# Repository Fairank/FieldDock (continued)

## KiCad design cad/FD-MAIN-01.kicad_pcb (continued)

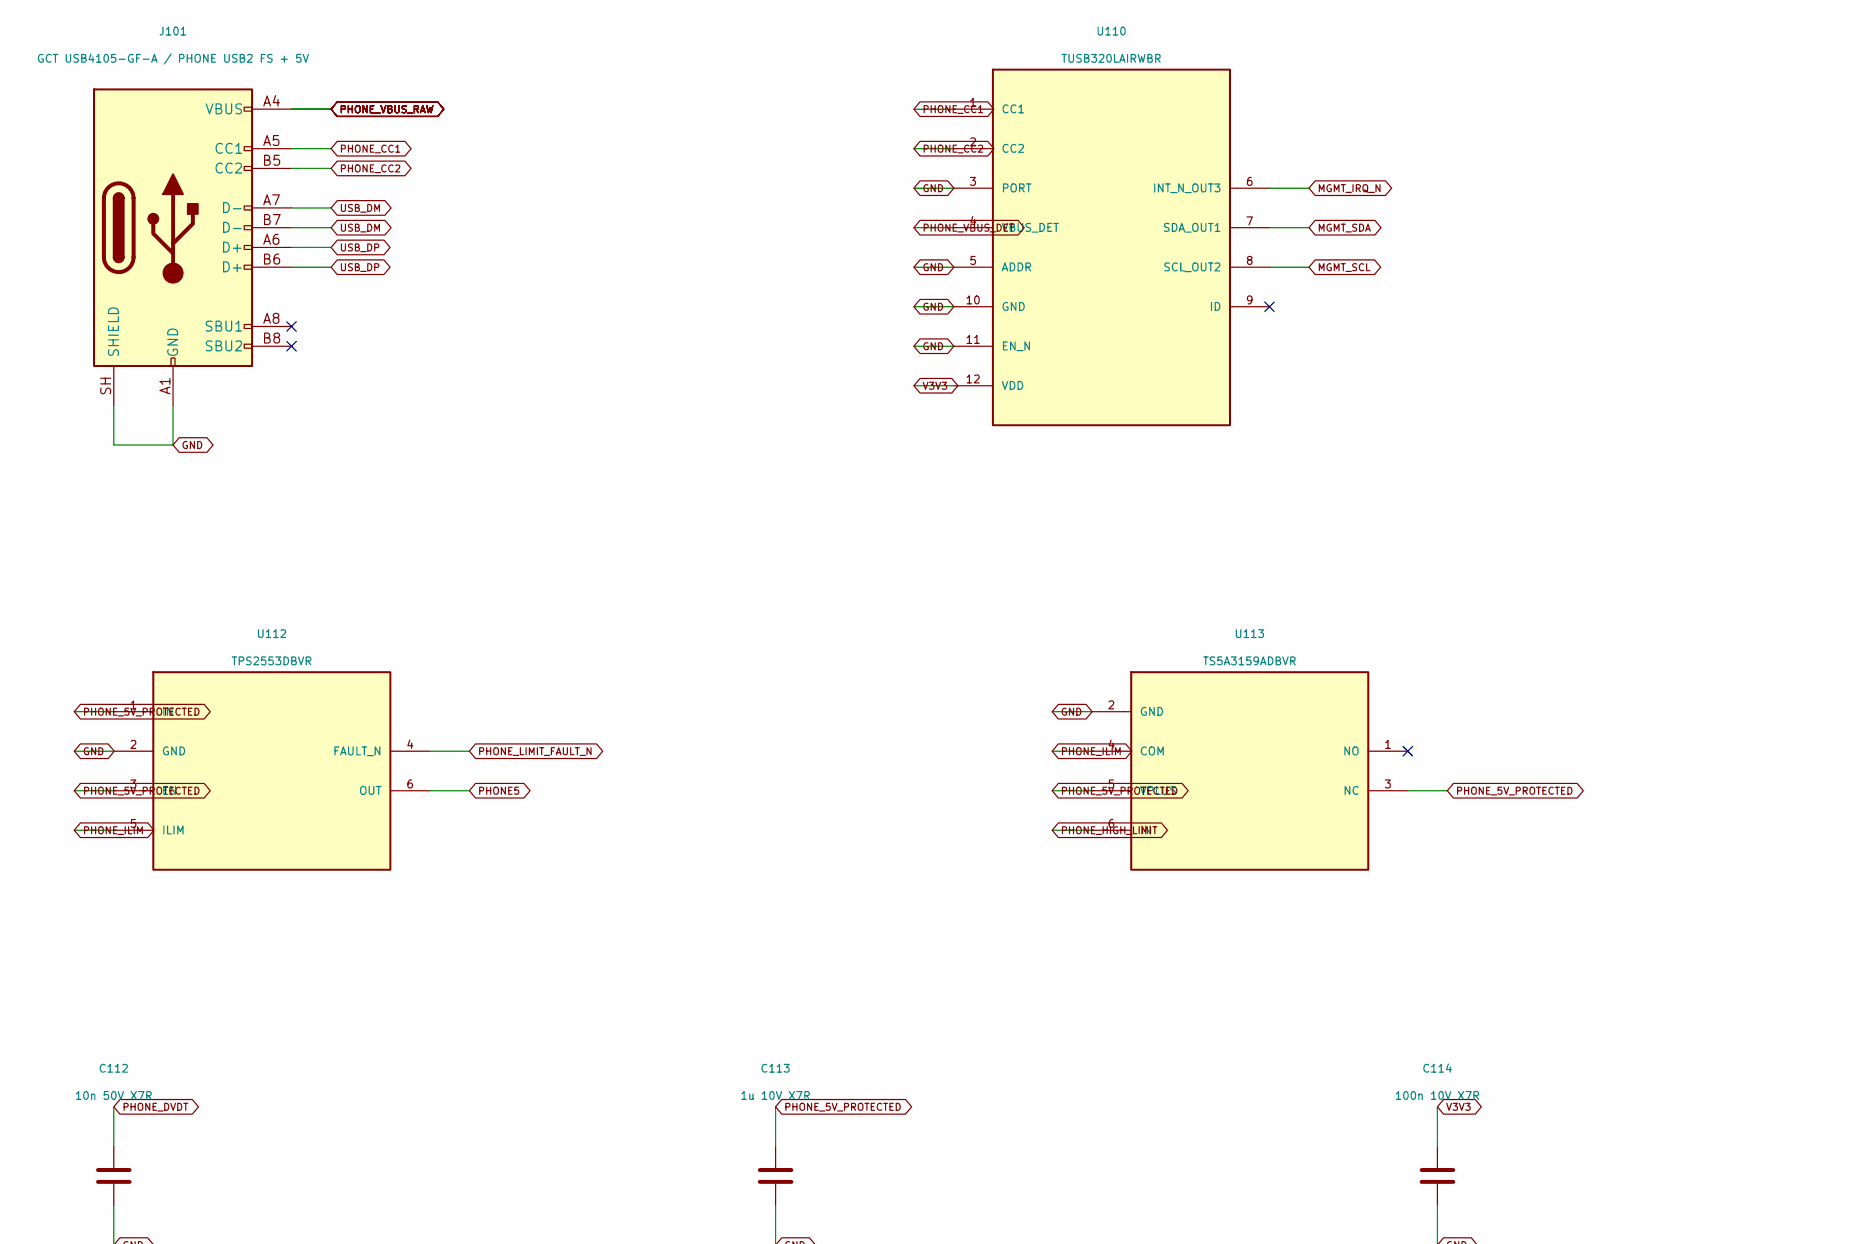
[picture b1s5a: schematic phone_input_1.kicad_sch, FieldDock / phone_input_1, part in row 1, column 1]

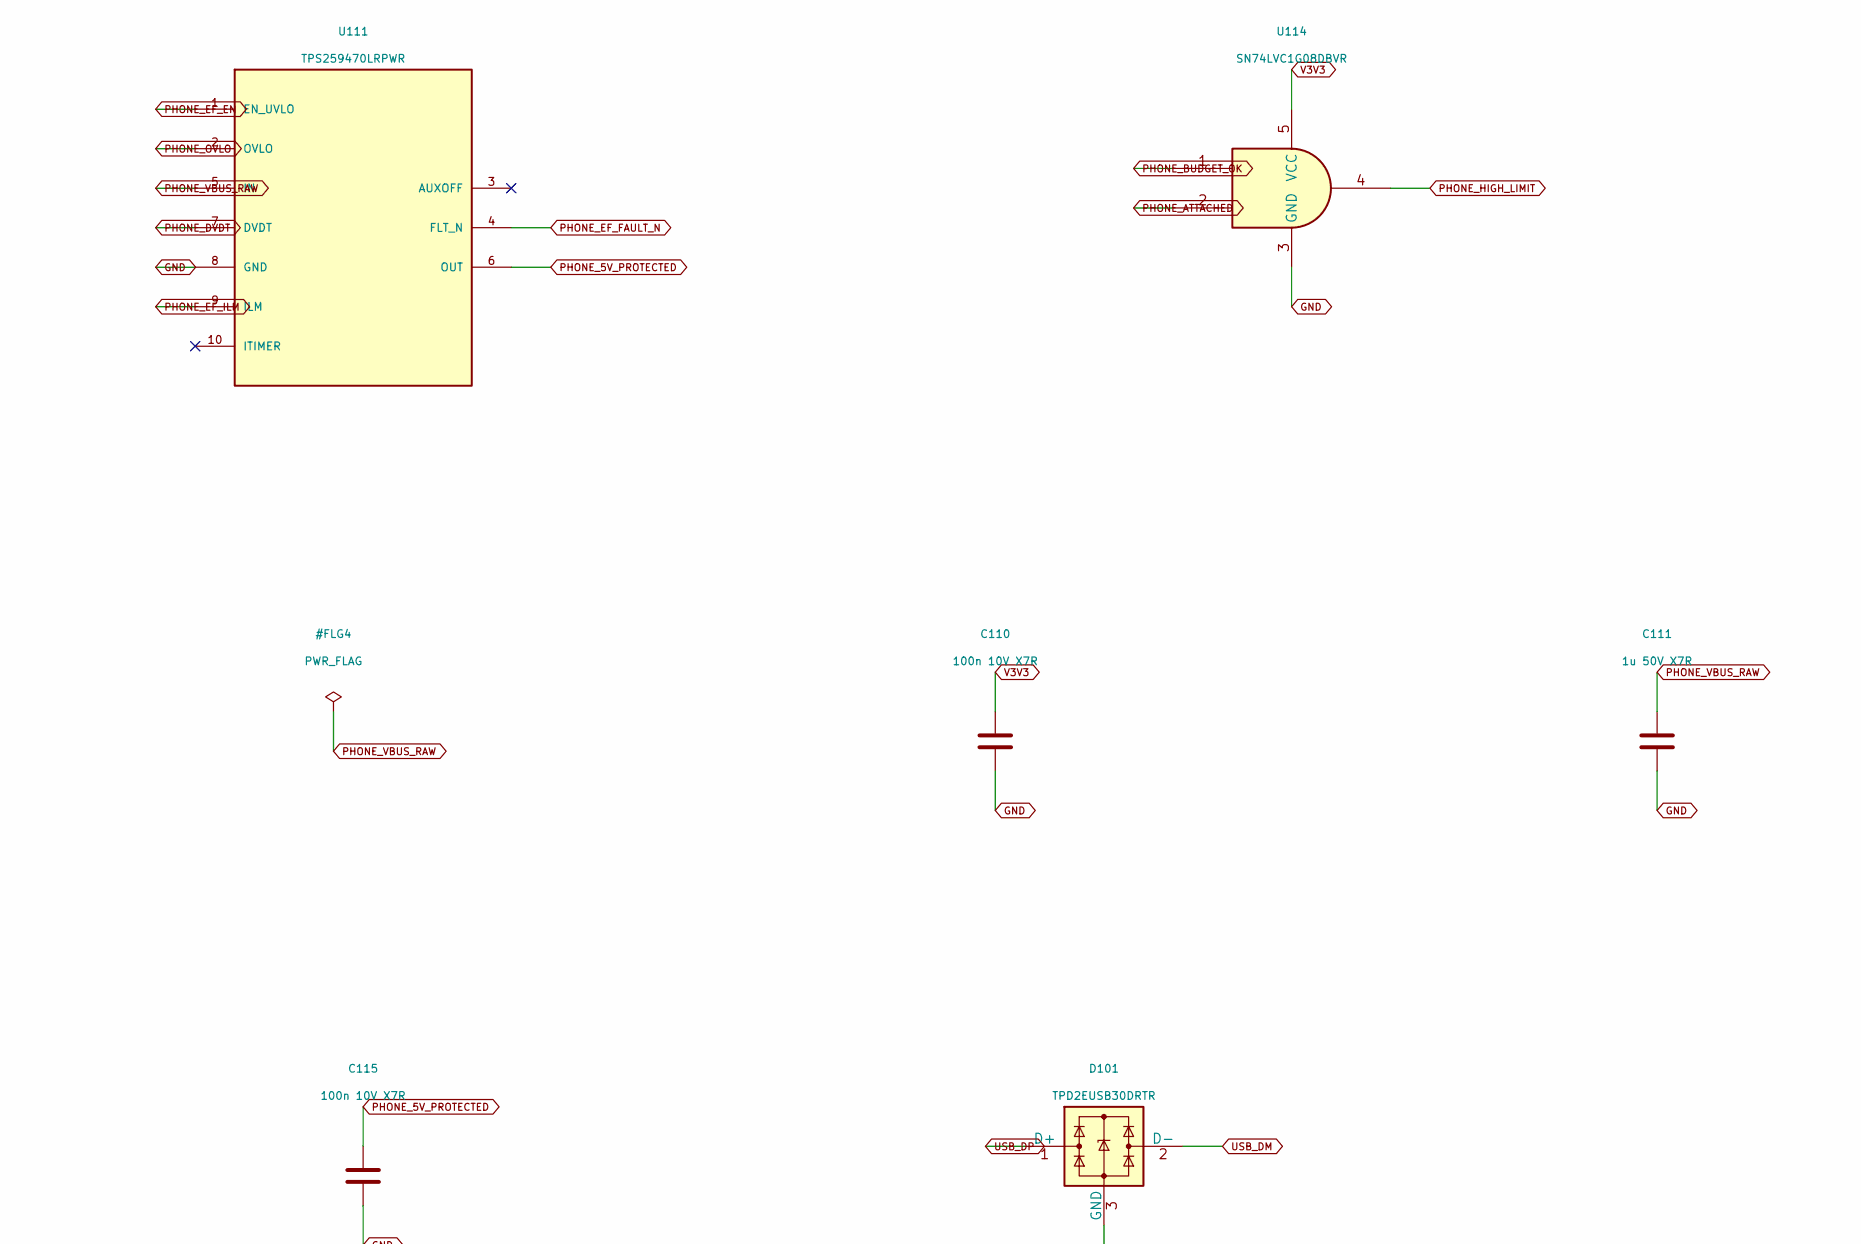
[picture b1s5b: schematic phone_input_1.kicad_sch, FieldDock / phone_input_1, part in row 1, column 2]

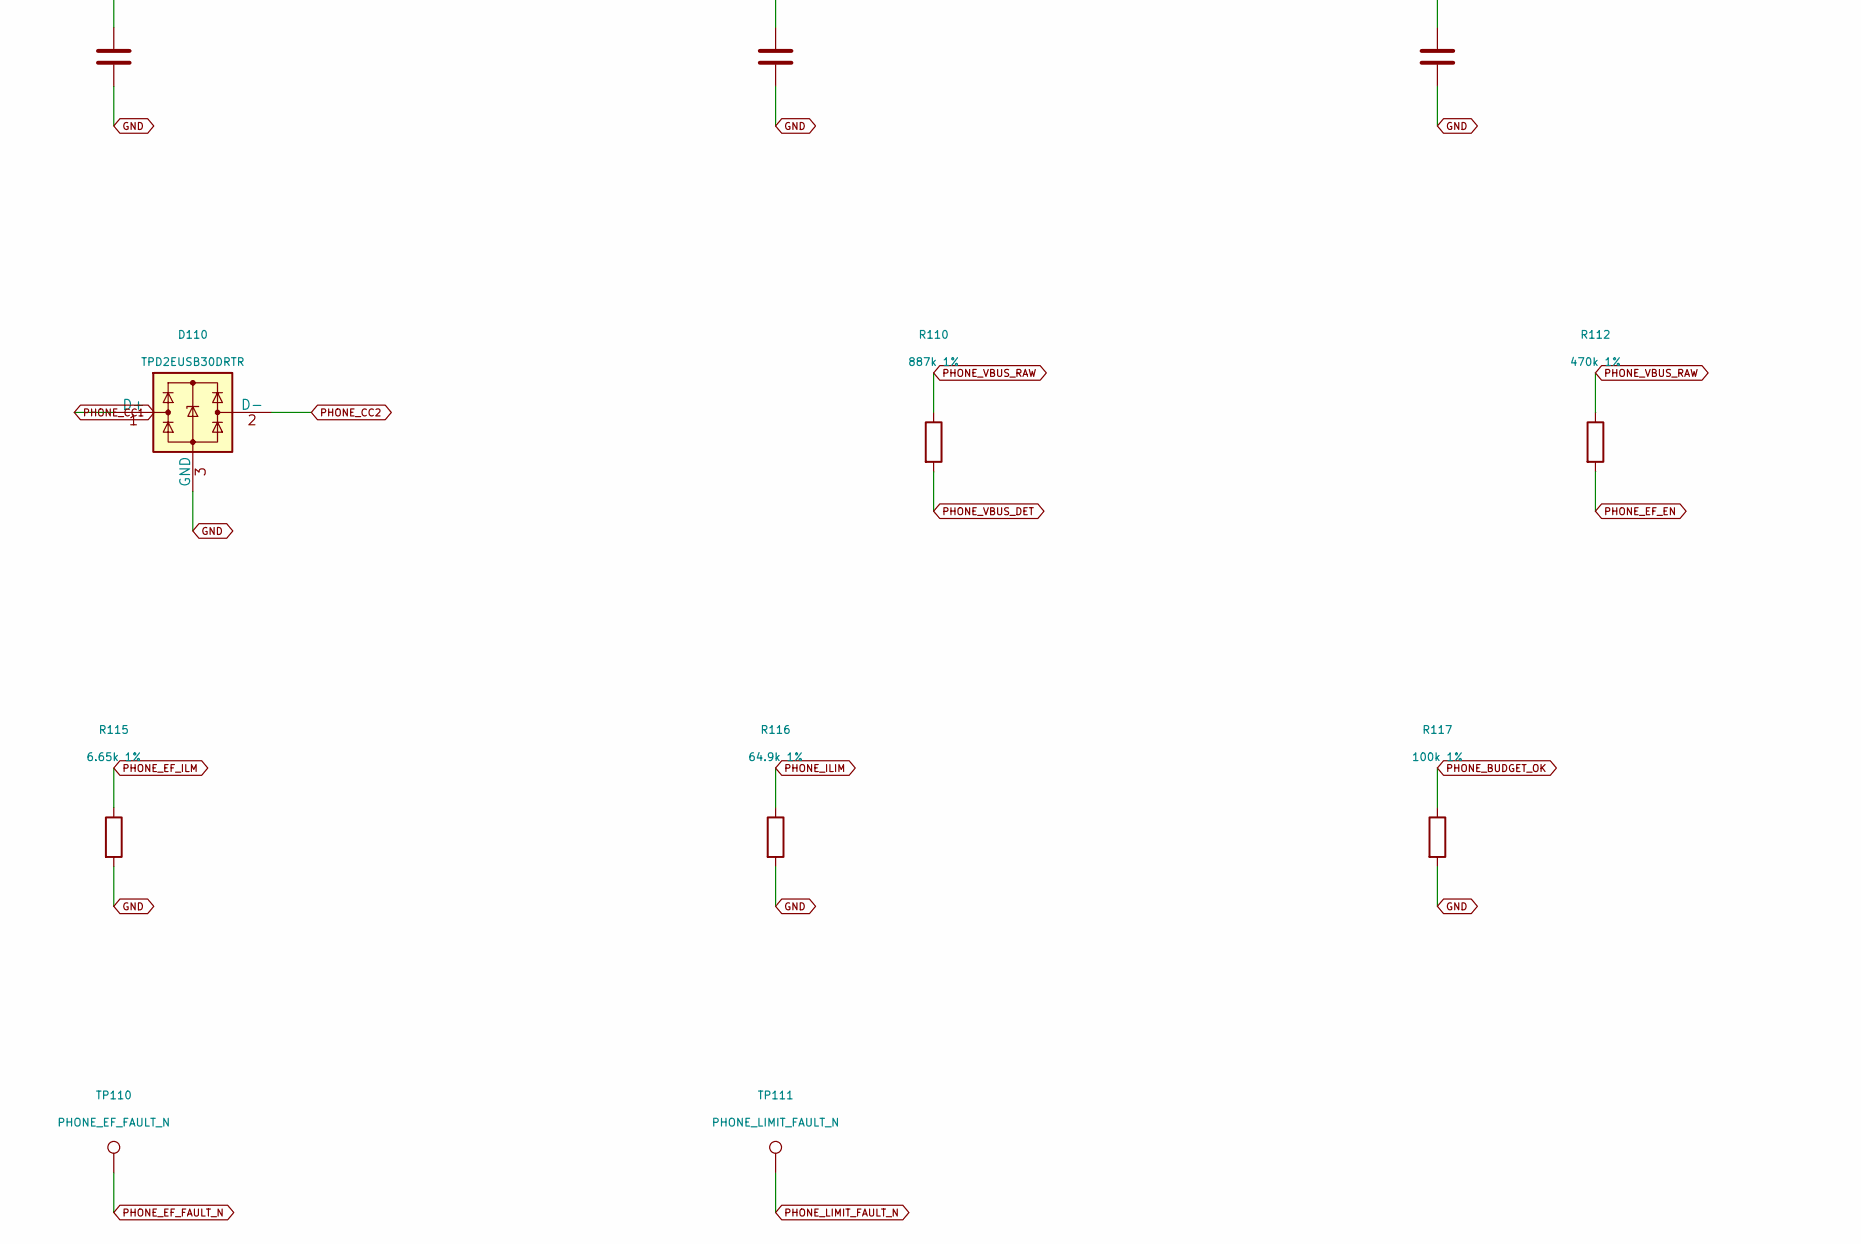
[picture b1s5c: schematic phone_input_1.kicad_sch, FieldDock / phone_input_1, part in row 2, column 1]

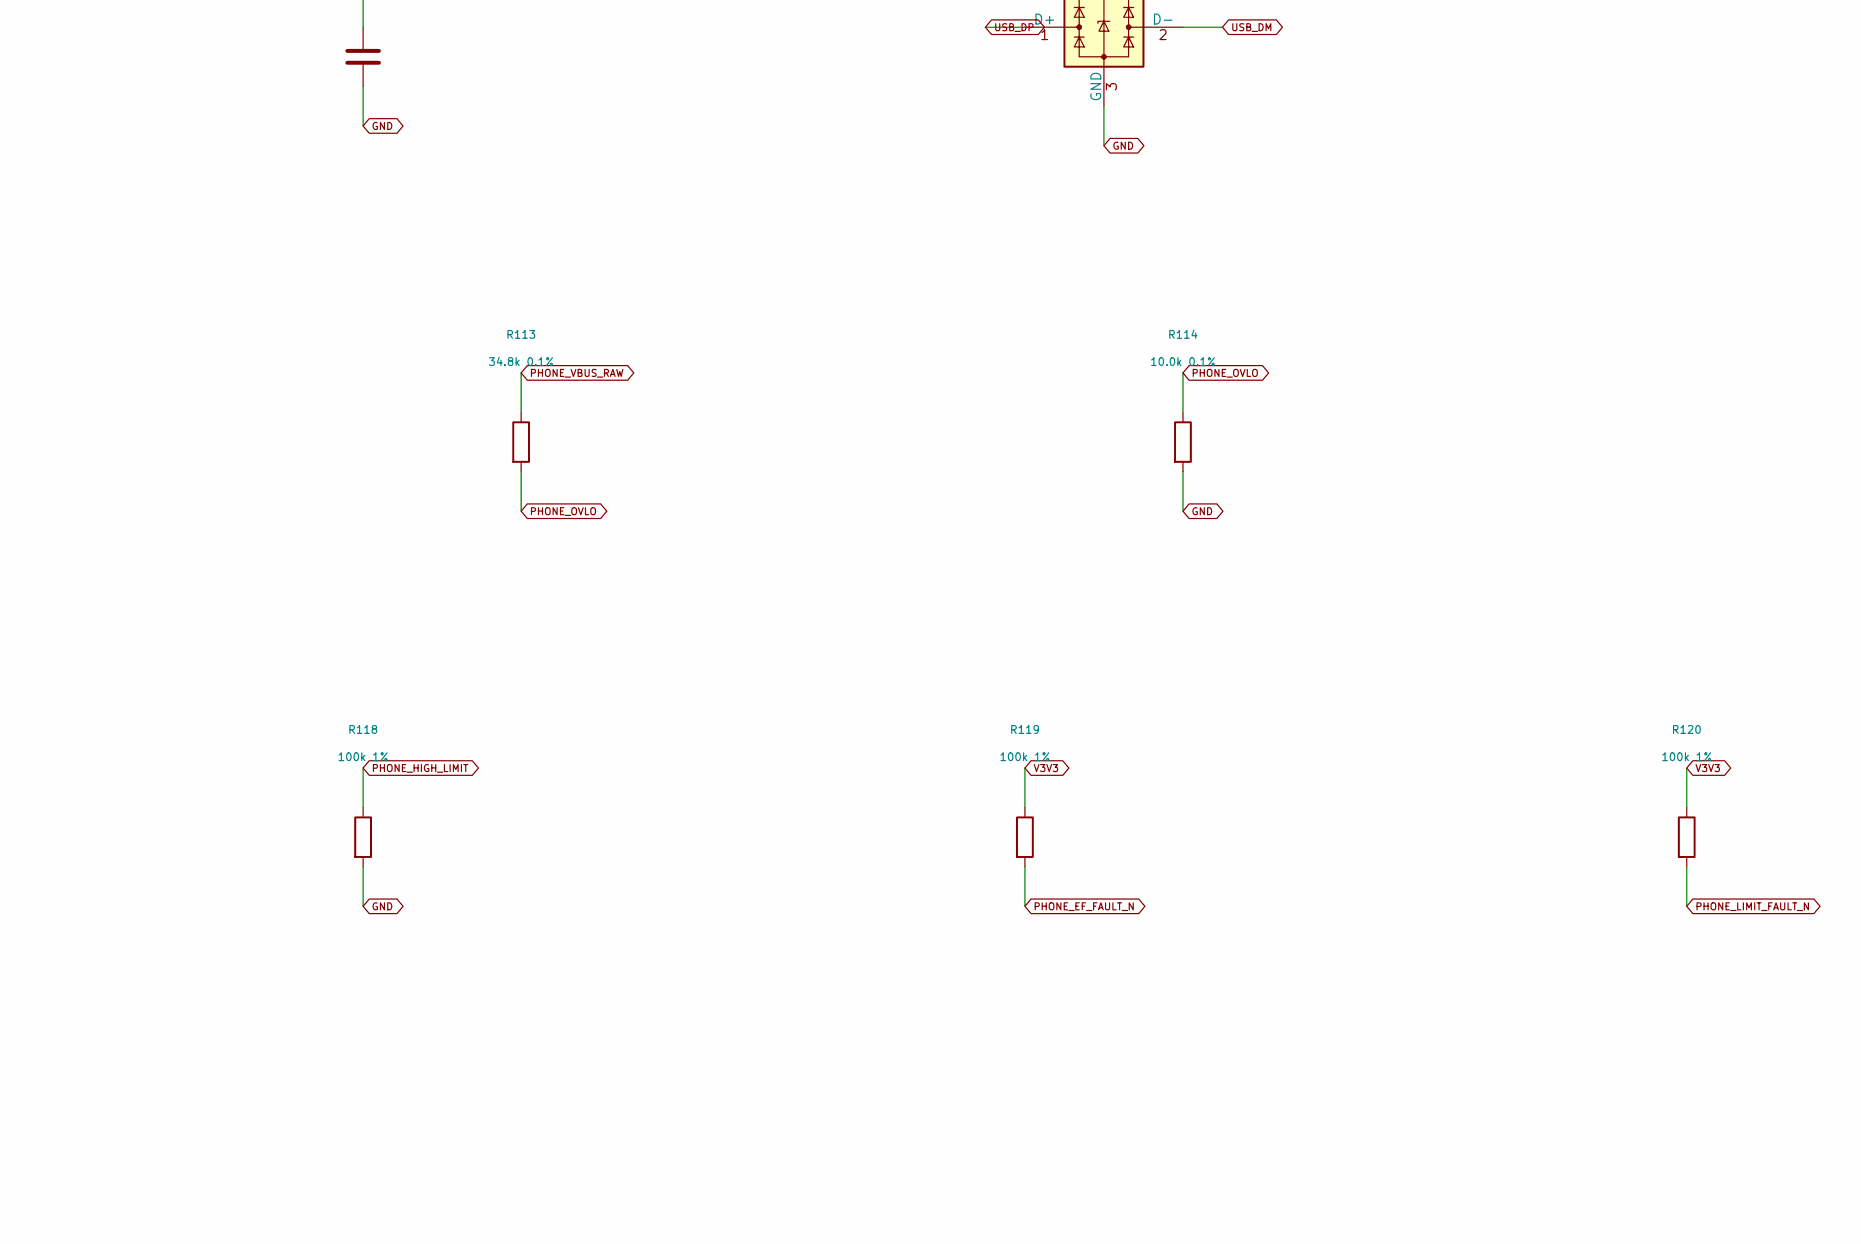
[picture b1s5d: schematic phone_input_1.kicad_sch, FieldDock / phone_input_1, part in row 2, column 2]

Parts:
C110, C114, C115: 100n 10V X7R; C_0603_1608Metric
C111: 1u 50V X7R; C_0805_2012Metric
C112: 10n 50V X7R; C_0603_1608Metric
C113: 1u 10V X7R; C_0603_1608Metric
D101, D110: TPD2EUSB30DRTR; Texas_DRT-3
J101: GCT USB4105-GF-A / PHONE USB2 FS + 5V; USB_C_Receptacle_GCT_USB4105-xx-A_16P_TopMnt_Horizontal
R110: 887k 1%; R_0402_1005Metric
R112: 470k 1%; R_0402_1005Metric
R113: 34.8k 0.1%; R_0402_1005Metric
R114: 10.0k 0.1%; R_0402_1005Metric
R115: 6.65k 1%; R_0402_1005Metric
R116: 64.9k 1%; R_0402_1005Metric
R117, R118, R119, R120: 100k 1%; R_0402_1005Metric
TP110: PHONE_EF_FAULT_N; TestPoint_Pad_D1.0mm
TP111: PHONE_LIMIT_FAULT_N; TestPoint_Pad_D1.0mm
U110: TUSB320LAIRWBR; Texas_X2QFN-12_1.6x1.6mm_P0.4mm
U111: TPS259470LRPWR; Texas_RPW0010A
U112: TPS2553DBVR; SOT-23-6
U113: TS5A3159ADBVR; SOT-23-6
U114: SN74LVC1G08DBVR; SOT-23-5

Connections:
GND: C110.2, C111.2, C112.2, C113.2, C114.2, C115.2, D101.3 (GND), D110.3 (GND), J101.A1 (GND), J101.A12 (GND), J101.B1 (GND), J101.B12 (GND), J101.SH (SHIELD), R114.2, R115.2, R116.2, R117.2, R118.2, U110.3 (PORT), U110.5 (ADDR), U110.10 (GND), U110.11 (EN_N), U111.8 (GND), U112.2 (GND), U113.2 (GND), U114.3 (GND); also elsewhere on the board
MGMT_IRQ_N: U110.6 (INT_N_OUT3); also elsewhere on the board
MGMT_SCL: U110.8 (SCL_OUT2); also elsewhere on the board
MGMT_SDA: U110.7 (SDA_OUT1); also elsewhere on the board
PHONE5: U112.6 (OUT); also elsewhere on the board
PHONE_5V_PROTECTED: C113.1, C115.1, U111.6 (OUT), U112.1 (IN), U112.3 (EN), U113.3 (NC), U113.5 (VPLUS)
PHONE_ATTACHED: U114.2; also elsewhere on the board
PHONE_BUDGET_OK: R117.1, U114.1; also elsewhere on the board
PHONE_CC1: D110.1 (D+), J101.A5 (CC1), U110.1 (CC1)
PHONE_CC2: D110.2 (D-), J101.B5 (CC2), U110.2 (CC2)
PHONE_DVDT: C112.1, U111.7 (DVDT)
PHONE_EF_EN: R112.2, U111.1 (EN_UVLO)
PHONE_EF_FAULT_N: R119.2, TP110.1, U111.4 (FLT_N)
PHONE_EF_ILM: R115.1, U111.9 (ILM)
PHONE_HIGH_LIMIT: R118.1, U113.6 (IN), U114.4
PHONE_ILIM: R116.1, U112.5 (ILIM), U113.4 (COM)
PHONE_LIMIT_FAULT_N: R120.2, TP111.1, U112.4 (FAULT_N)
PHONE_OVLO: R113.2, R114.1, U111.2 (OVLO)
PHONE_VBUS_DET: R110.2, U110.4 (VBUS_DET)
PHONE_VBUS_RAW: C111.1, J101.A4 (VBUS), J101.A9 (VBUS), J101.B4 (VBUS), J101.B9 (VBUS), R110.1, R112.1, R113.1, U111.5 (IN); also elsewhere on the board
USB_DM: D101.2 (D-), J101.A7 (D-), J101.B7 (D-); also elsewhere on the board
USB_DP: D101.1 (D+), J101.A6 (D+), J101.B6 (D+); also elsewhere on the board
V3V3: C110.1, C114.1, R119.1, R120.1, U110.12 (VDD), U114.5 (VCC); also elsewhere on the board

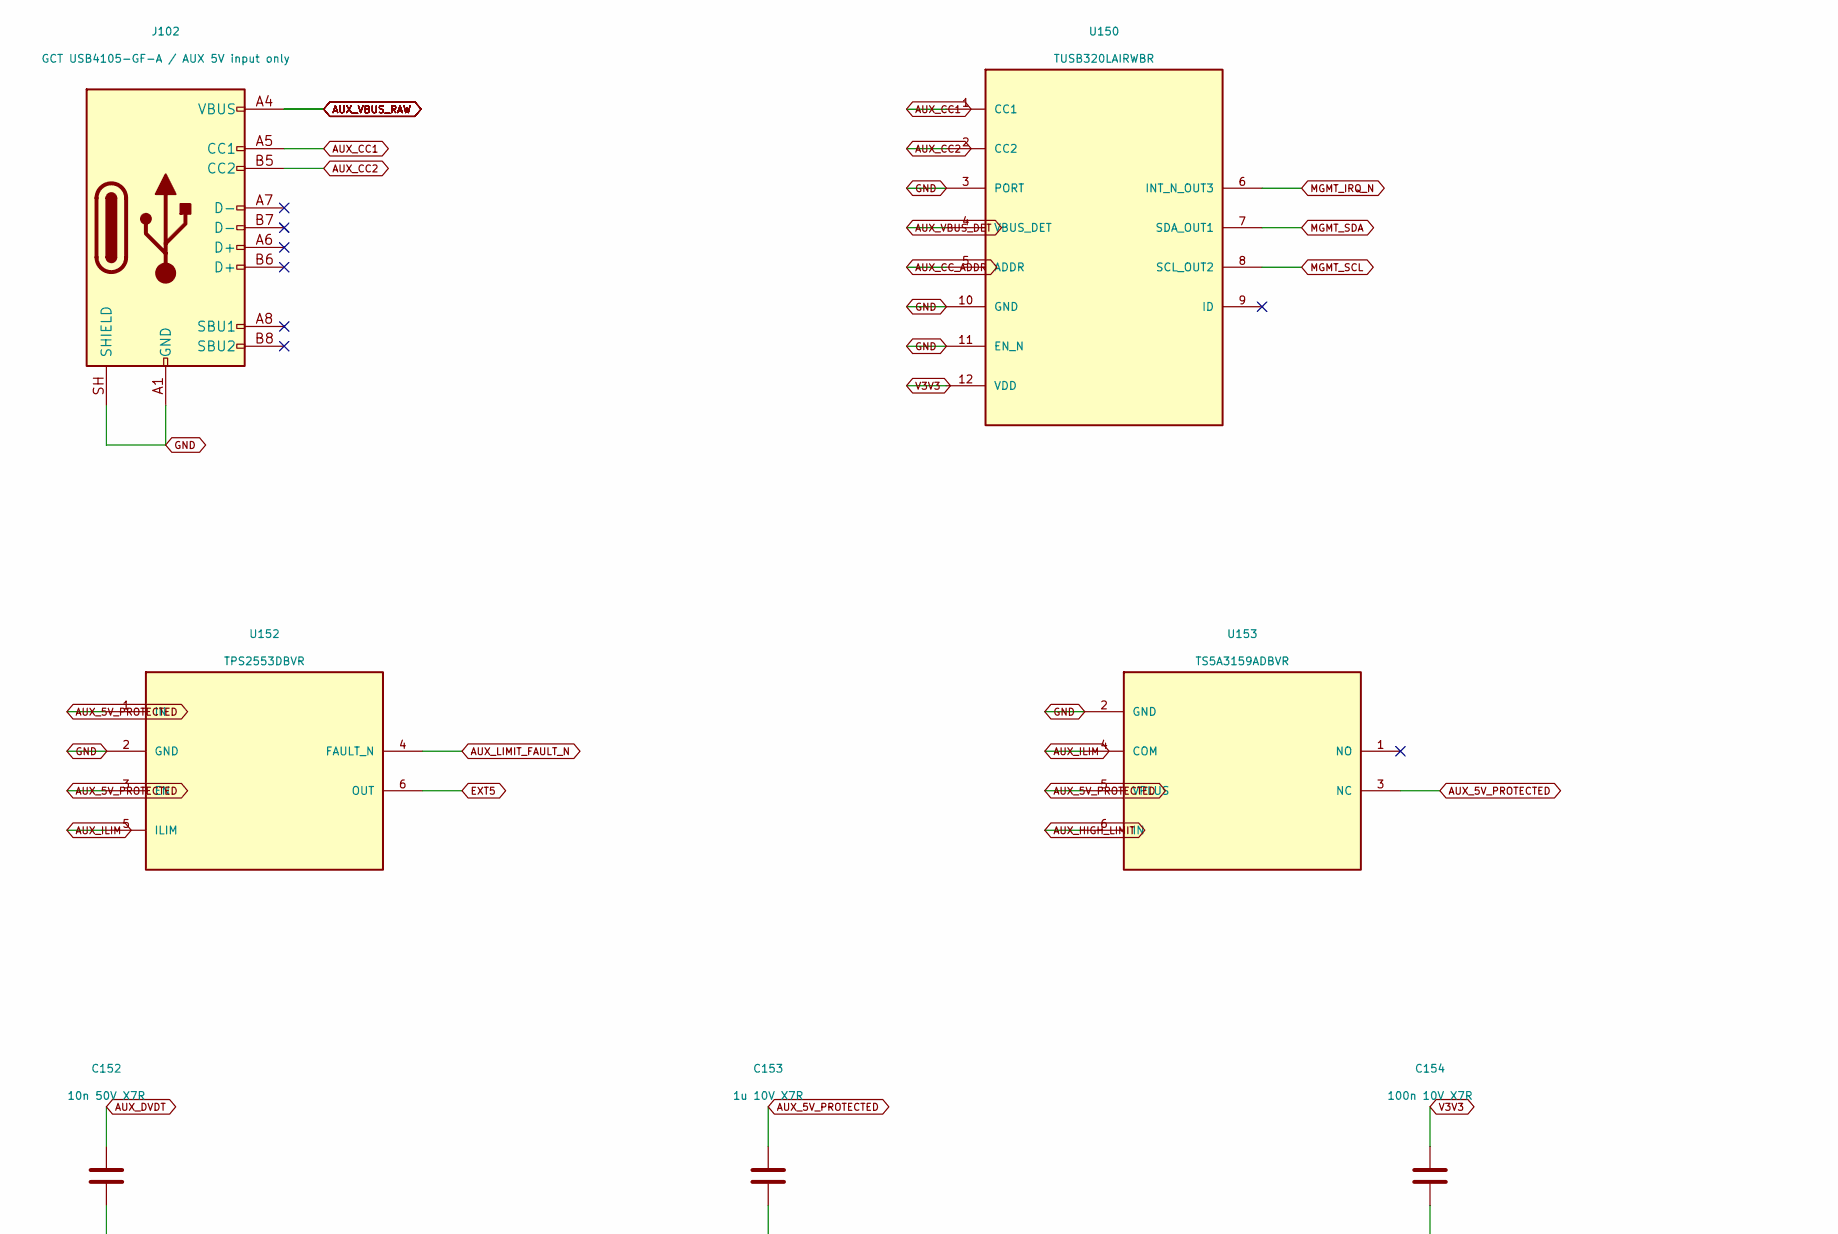
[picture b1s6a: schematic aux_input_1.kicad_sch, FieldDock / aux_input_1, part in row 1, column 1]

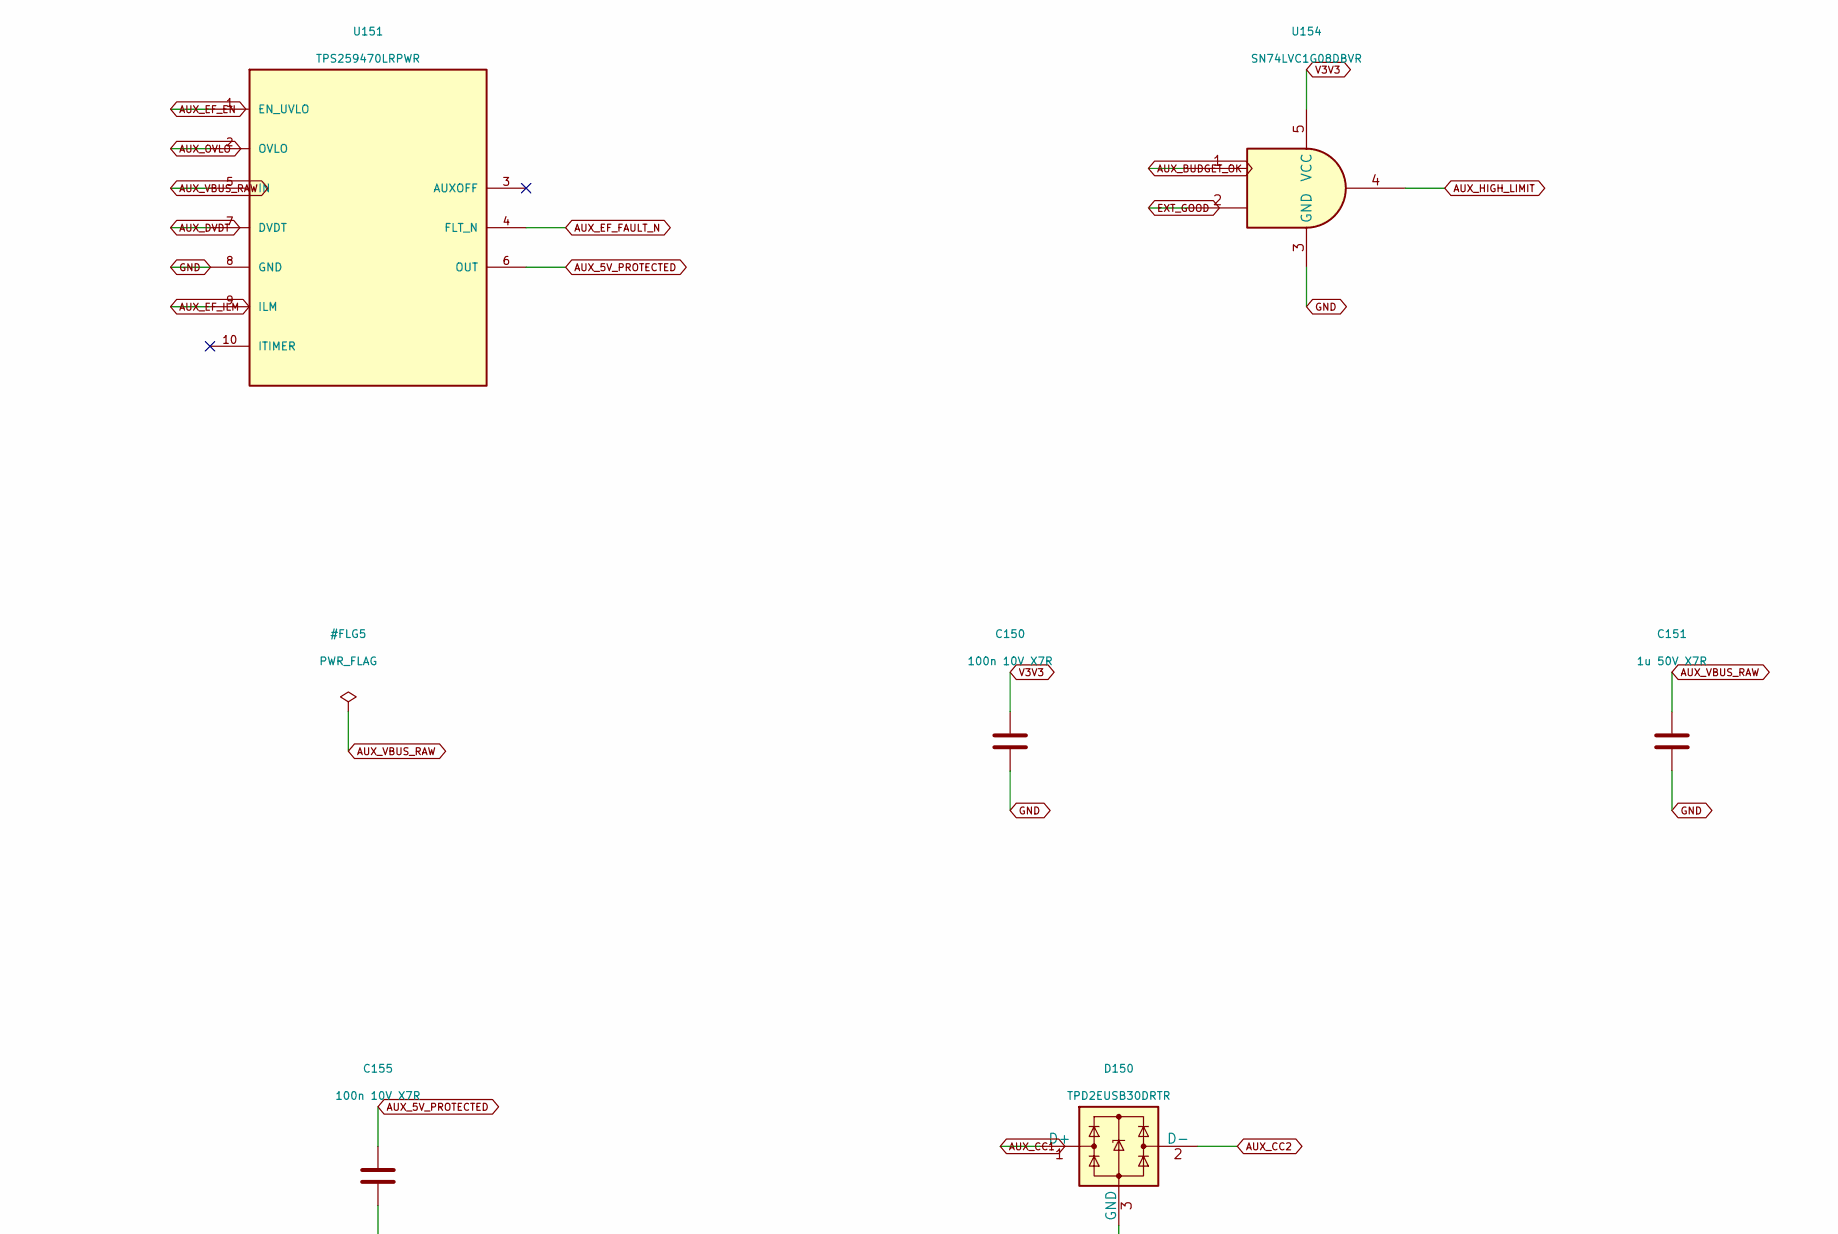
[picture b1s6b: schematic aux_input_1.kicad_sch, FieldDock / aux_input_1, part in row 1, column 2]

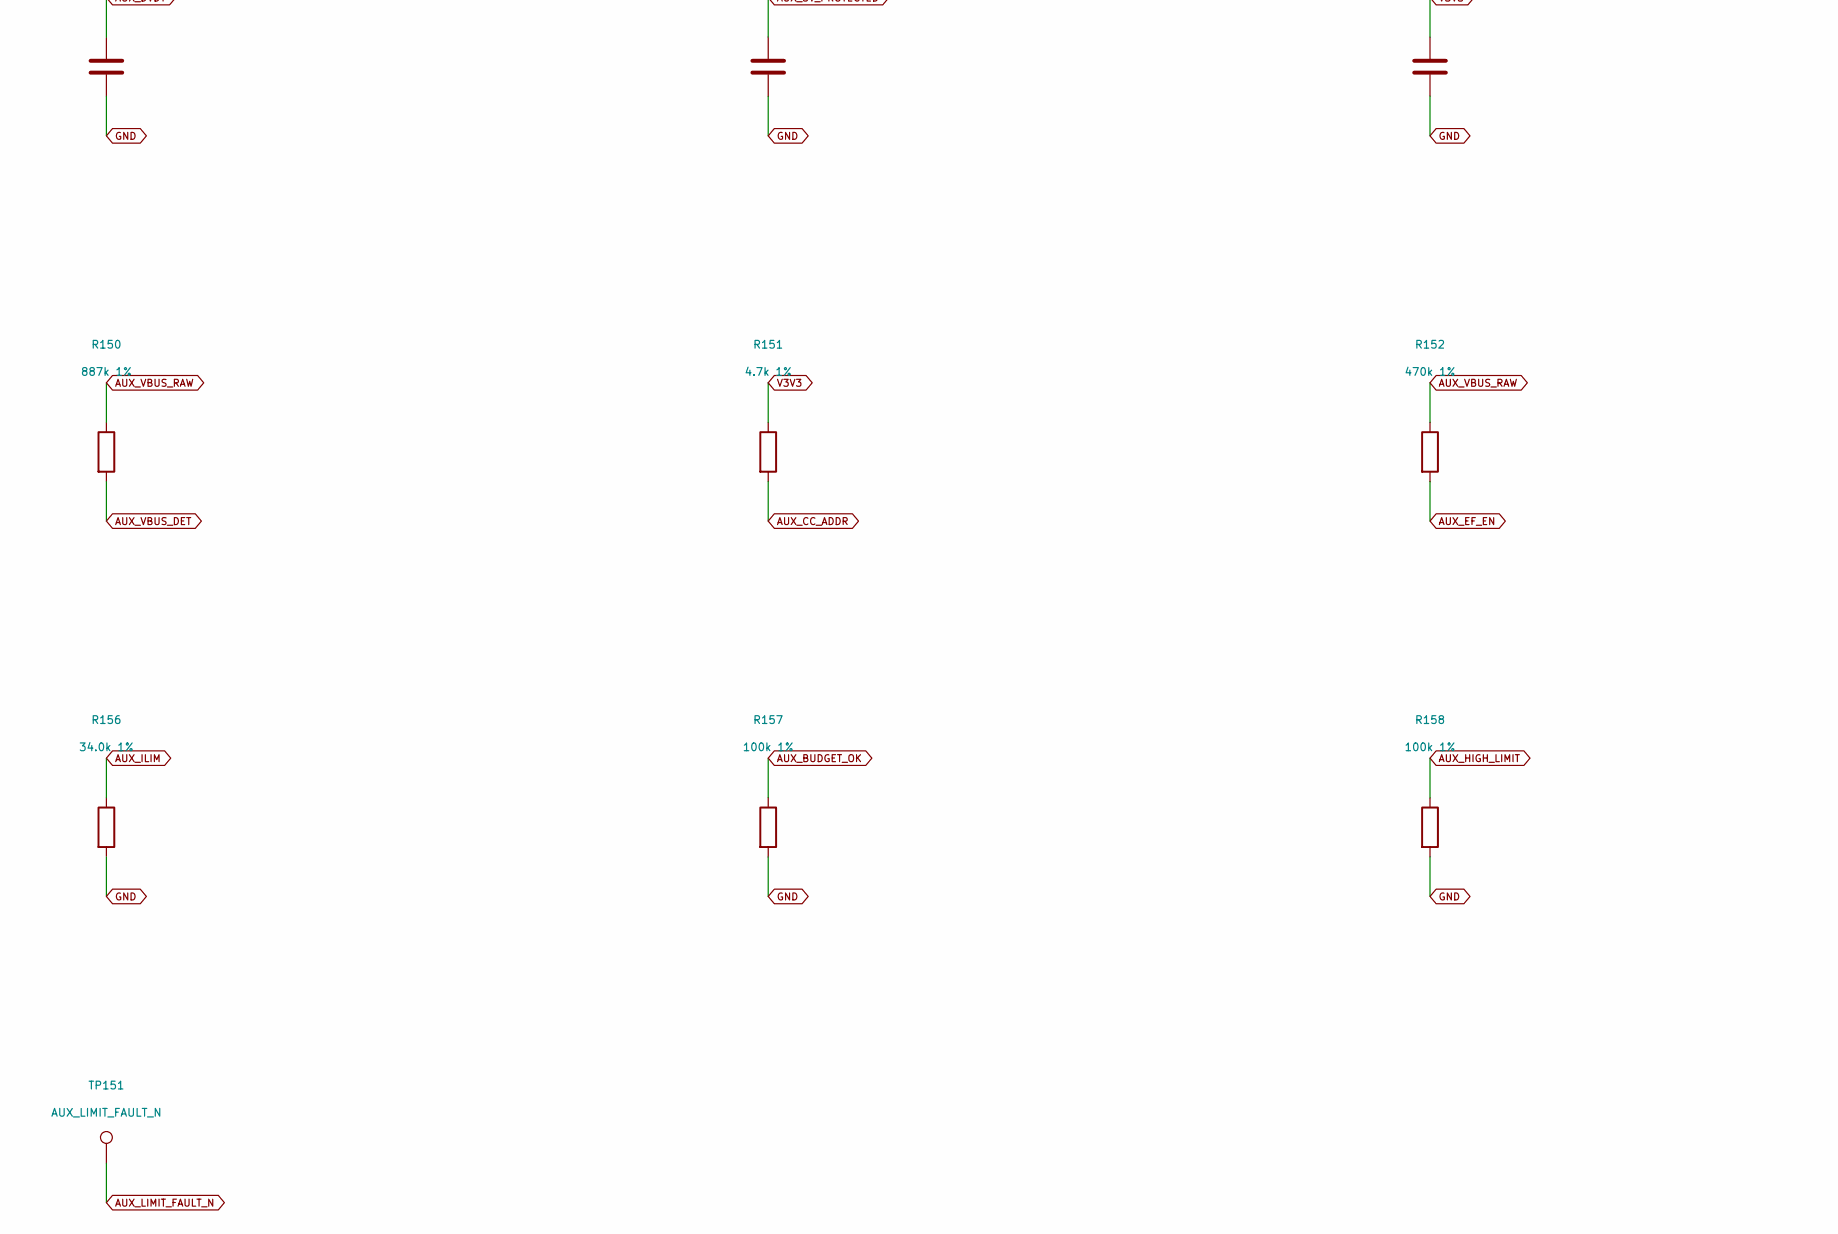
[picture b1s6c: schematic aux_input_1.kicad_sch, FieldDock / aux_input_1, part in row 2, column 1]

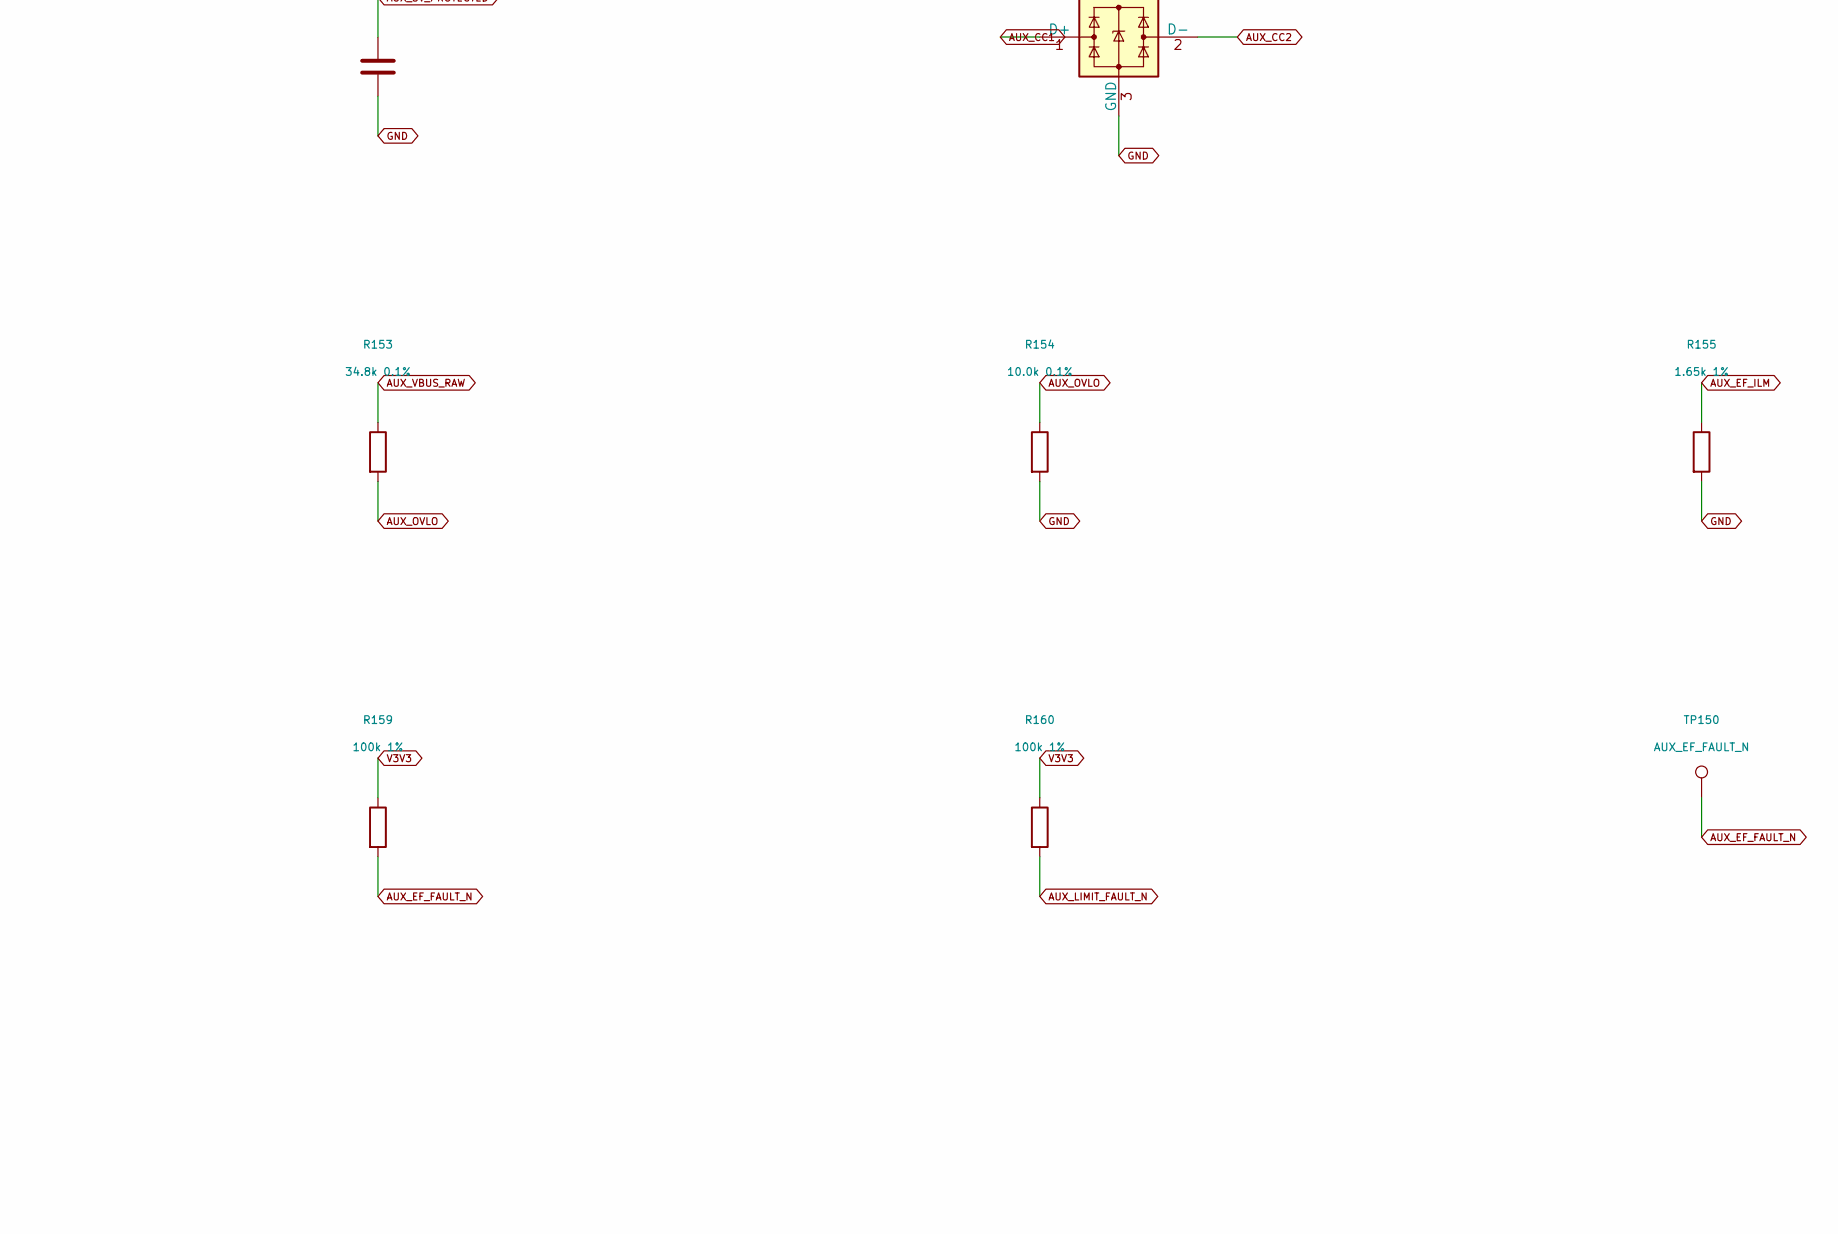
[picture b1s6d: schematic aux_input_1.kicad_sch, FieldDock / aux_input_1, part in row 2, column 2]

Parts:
C150, C154, C155: 100n 10V X7R; C_0603_1608Metric
C151: 1u 50V X7R; C_0805_2012Metric
C152: 10n 50V X7R; C_0603_1608Metric
C153: 1u 10V X7R; C_0603_1608Metric
D150: TPD2EUSB30DRTR; Texas_DRT-3
J102: GCT USB4105-GF-A / AUX 5V input only; USB_C_Receptacle_GCT_USB4105-xx-A_16P_TopMnt_Horizontal
R150: 887k 1%; R_0402_1005Metric
R151: 4.7k 1%; R_0402_1005Metric
R152: 470k 1%; R_0402_1005Metric
R153: 34.8k 0.1%; R_0402_1005Metric
R154: 10.0k 0.1%; R_0402_1005Metric
R155: 1.65k 1%; R_0402_1005Metric
R156: 34.0k 1%; R_0402_1005Metric
R157, R158, R159, R160: 100k 1%; R_0402_1005Metric
TP150: AUX_EF_FAULT_N; TestPoint_Pad_D1.0mm
TP151: AUX_LIMIT_FAULT_N; TestPoint_Pad_D1.0mm
U150: TUSB320LAIRWBR; Texas_X2QFN-12_1.6x1.6mm_P0.4mm
U151: TPS259470LRPWR; Texas_RPW0010A
U152: TPS2553DBVR; SOT-23-6
U153: TS5A3159ADBVR; SOT-23-6
U154: SN74LVC1G08DBVR; SOT-23-5

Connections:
AUX_5V_PROTECTED: C153.1, C155.1, U151.6 (OUT), U152.1 (IN), U152.3 (EN), U153.3 (NC), U153.5 (VPLUS); also elsewhere on the board
AUX_BUDGET_OK: R157.1, U154.1; also elsewhere on the board
AUX_CC1: D150.1 (D+), J102.A5 (CC1), U150.1 (CC1)
AUX_CC2: D150.2 (D-), J102.B5 (CC2), U150.2 (CC2)
AUX_CC_ADDR: R151.2, U150.5 (ADDR)
AUX_DVDT: C152.1, U151.7 (DVDT)
AUX_EF_EN: R152.2, U151.1 (EN_UVLO)
AUX_EF_FAULT_N: R159.2, TP150.1, U151.4 (FLT_N)
AUX_EF_ILM: R155.1, U151.9 (ILM)
AUX_HIGH_LIMIT: R158.1, U153.6 (IN), U154.4
AUX_ILIM: R156.1, U152.5 (ILIM), U153.4 (COM)
AUX_LIMIT_FAULT_N: R160.2, TP151.1, U152.4 (FAULT_N)
AUX_OVLO: R153.2, R154.1, U151.2 (OVLO)
AUX_VBUS_DET: R150.2, U150.4 (VBUS_DET)
AUX_VBUS_RAW: C151.1, J102.A4 (VBUS), J102.A9 (VBUS), J102.B4 (VBUS), J102.B9 (VBUS), R150.1, R152.1, R153.1, U151.5 (IN); also elsewhere on the board
EXT5: U152.6 (OUT); also elsewhere on the board
EXT_GOOD: U154.2; also elsewhere on the board
GND: C150.2, C151.2, C152.2, C153.2, C154.2, C155.2, D150.3 (GND), J102.A1 (GND), J102.A12 (GND), J102.B1 (GND), J102.B12 (GND), J102.SH (SHIELD), R154.2, R155.2, R156.2, R157.2, R158.2, U150.3 (PORT), U150.10 (GND), U150.11 (EN_N), U151.8 (GND), U152.2 (GND), U153.2 (GND), U154.3 (GND); also elsewhere on the board
MGMT_IRQ_N: U150.6 (INT_N_OUT3); also elsewhere on the board
MGMT_SCL: U150.8 (SCL_OUT2); also elsewhere on the board
MGMT_SDA: U150.7 (SDA_OUT1); also elsewhere on the board
V3V3: C150.1, C154.1, R151.1, R159.1, R160.1, U150.12 (VDD), U154.5 (VCC); also elsewhere on the board
